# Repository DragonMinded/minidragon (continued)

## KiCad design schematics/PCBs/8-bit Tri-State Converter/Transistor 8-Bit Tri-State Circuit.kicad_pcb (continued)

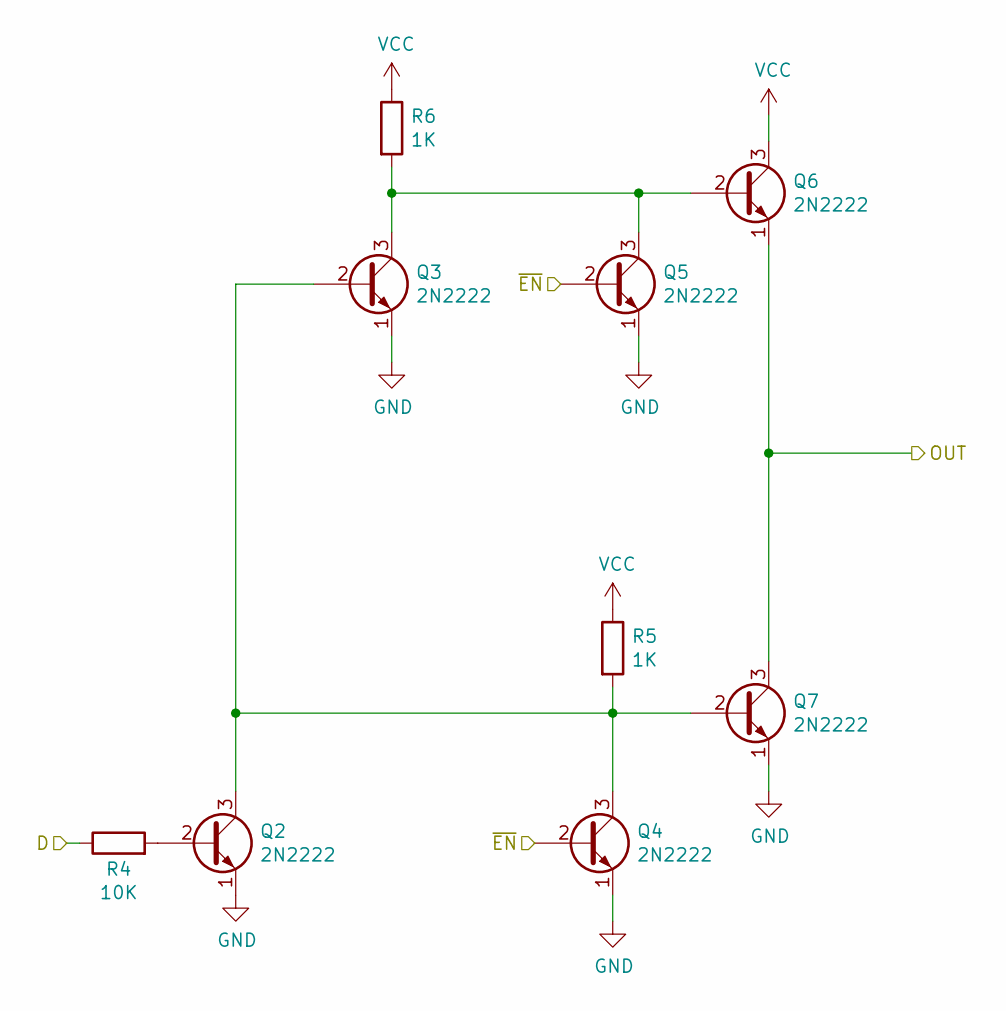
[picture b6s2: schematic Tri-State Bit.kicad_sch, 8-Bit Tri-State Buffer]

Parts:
Q2, Q3, Q4, Q5, Q6, Q7: 2N2222; TO-92_Inline
R4: 10K; R_Axial_DIN0309_L9.0mm_D3.2mm_P12.70mm_Horizontal
R5, R6: 1K; R_Axial_DIN0309_L9.0mm_D3.2mm_P12.70mm_Horizontal

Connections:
D0: R4.1; also elsewhere on the board
GND: Q2.1 (E), Q3.1 (E), Q4.1 (E), Q5.1 (E), Q7.1 (E); also elsewhere on the board
unnamed: Q2.2 (B), R4.2
unnamed: Q2.3 (C), Q3.2 (B), Q4.3 (C), Q7.2 (B), R5.2
unnamed: Q3.3 (C), Q5.3 (C), Q6.2 (B), R6.2
Q0: Q6.1 (E), Q7.3 (C); also elsewhere on the board
VCC: Q6.3 (C), R5.1, R6.1; also elsewhere on the board
~EN_BUF: Q4.2 (B), Q5.2 (B); also elsewhere on the board

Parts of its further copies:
Q8, Q9, Q10, Q11, Q12, Q13, Q14, Q15, Q16, Q17, Q18, Q19, Q20, Q21, Q22, Q23, Q24, Q25, Q26, Q27, Q28, Q29, Q30, Q31, Q32, Q33, Q34, Q35, Q36, Q37, Q38, Q39, Q40, Q41, Q42, Q43, Q44, Q45, Q46, Q47, Q48, Q49: 2N2222; TO-92_Inline
R7, R10, R13, R16, R19, R22, R25: 10K; R_Axial_DIN0309_L9.0mm_D3.2mm_P12.70mm_Horizontal
R8, R9, R11, R12, R14, R15, R17, R18, R20, R21, R23, R24, R26, R27: 1K; R_Axial_DIN0309_L9.0mm_D3.2mm_P12.70mm_Horizontal

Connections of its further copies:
D1: R7.1; also elsewhere on the board
D2: R10.1; also elsewhere on the board
D3: R13.1; also elsewhere on the board
D4: R16.1; also elsewhere on the board
D5: R19.1; also elsewhere on the board
D6: R22.1; also elsewhere on the board
D7: R25.1; also elsewhere on the board
GND: Q8.1 (E), Q9.1 (E), Q10.1 (E), Q11.1 (E), Q13.1 (E), Q14.1 (E), Q15.1 (E), Q16.1 (E), Q17.1 (E), Q19.1 (E), Q20.1 (E), Q21.1 (E), Q22.1 (E), Q23.1 (E), Q25.1 (E), Q26.1 (E), Q27.1 (E), Q28.1 (E), Q29.1 (E), Q31.1 (E), Q32.1 (E), Q33.1 (E), Q34.1 (E), Q35.1 (E), Q37.1 (E), Q38.1 (E), Q39.1 (E), Q40.1 (E), Q41.1 (E), Q43.1 (E), Q44.1 (E), Q45.1 (E), Q46.1 (E), Q47.1 (E), Q49.1 (E); also elsewhere on the board
unnamed: Q8.2 (B), R7.2
unnamed: Q8.3 (C), Q9.2 (B), Q10.3 (C), Q13.2 (B), R8.2
unnamed: Q9.3 (C), Q11.3 (C), Q12.2 (B), R9.2
unnamed: Q14.2 (B), R10.2
unnamed: Q14.3 (C), Q15.2 (B), Q16.3 (C), Q19.2 (B), R11.2
unnamed: Q15.3 (C), Q17.3 (C), Q18.2 (B), R12.2
unnamed: Q20.2 (B), R13.2
unnamed: Q20.3 (C), Q21.2 (B), Q22.3 (C), Q25.2 (B), R14.2
unnamed: Q21.3 (C), Q23.3 (C), Q24.2 (B), R15.2
unnamed: Q26.2 (B), R16.2
unnamed: Q26.3 (C), Q27.2 (B), Q28.3 (C), Q31.2 (B), R17.2
unnamed: Q27.3 (C), Q29.3 (C), Q30.2 (B), R18.2
unnamed: Q32.2 (B), R19.2
unnamed: Q32.3 (C), Q33.2 (B), Q34.3 (C), Q37.2 (B), R20.2
unnamed: Q33.3 (C), Q35.3 (C), Q36.2 (B), R21.2
unnamed: Q38.2 (B), R22.2
unnamed: Q38.3 (C), Q39.2 (B), Q40.3 (C), Q43.2 (B), R23.2
unnamed: Q39.3 (C), Q41.3 (C), Q42.2 (B), R24.2
unnamed: Q44.2 (B), R25.2
unnamed: Q44.3 (C), Q45.2 (B), Q46.3 (C), Q49.2 (B), R26.2
unnamed: Q45.3 (C), Q47.3 (C), Q48.2 (B), R27.2
Q1: Q12.1 (E), Q13.3 (C); also elsewhere on the board
Q2: Q18.1 (E), Q19.3 (C); also elsewhere on the board
Q3: Q24.1 (E), Q25.3 (C); also elsewhere on the board
Q4: Q30.1 (E), Q31.3 (C); also elsewhere on the board
Q5: Q36.1 (E), Q37.3 (C); also elsewhere on the board
Q6: Q42.1 (E), Q43.3 (C); also elsewhere on the board
Q7: Q48.1 (E), Q49.3 (C); also elsewhere on the board
VCC: Q12.3 (C), Q18.3 (C), Q24.3 (C), Q30.3 (C), Q36.3 (C), Q42.3 (C), Q48.3 (C), R8.1, R9.1, R11.1, R12.1, R14.1, R15.1, R17.1, R18.1, R20.1, R21.1, R23.1, R24.1, R26.1, R27.1; also elsewhere on the board
~EN_BUF: Q10.2 (B), Q11.2 (B), Q16.2 (B), Q17.2 (B), Q22.2 (B), Q23.2 (B), Q28.2 (B), Q29.2 (B), Q34.2 (B), Q35.2 (B), Q40.2 (B), Q41.2 (B), Q46.2 (B), Q47.2 (B); also elsewhere on the board

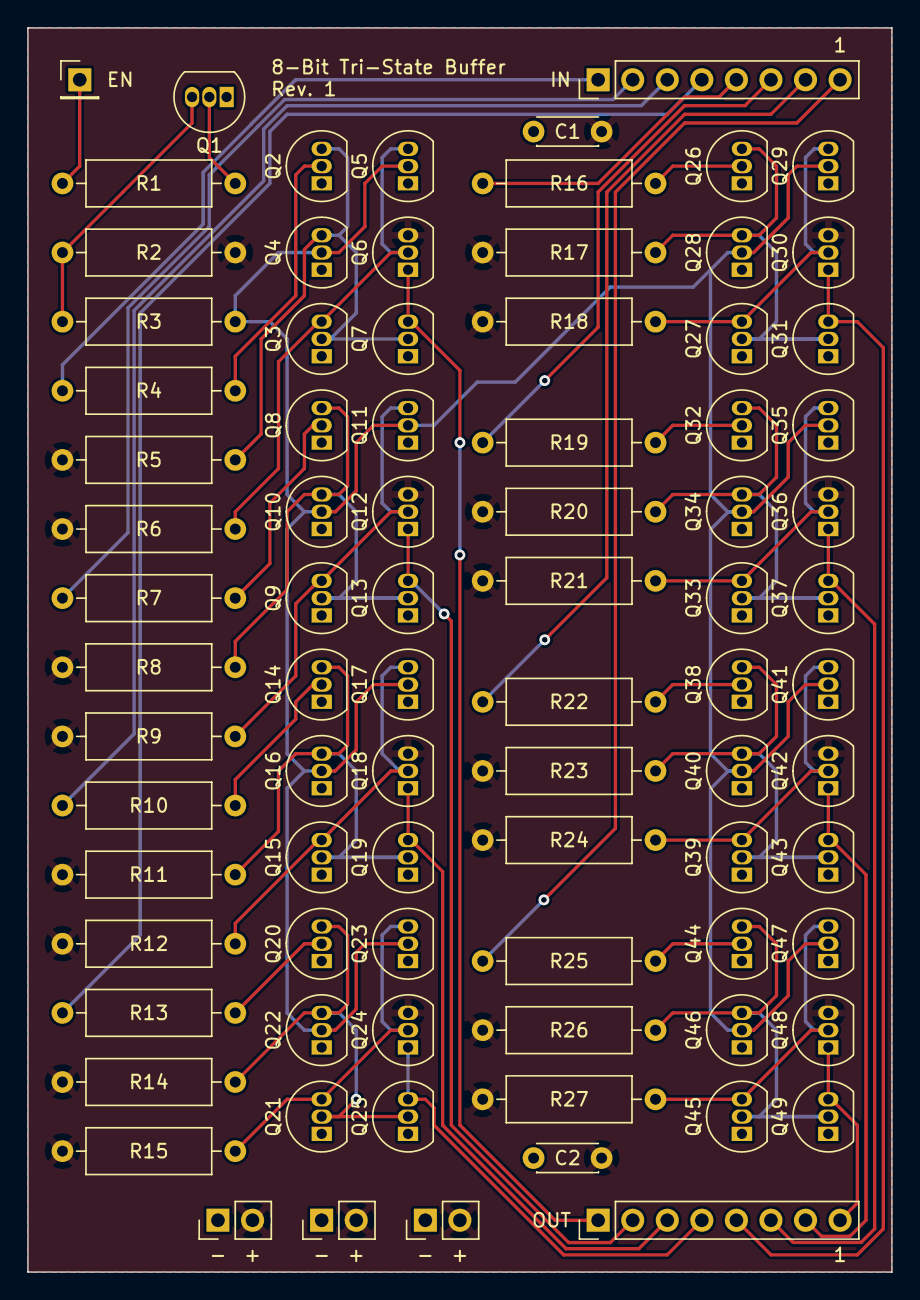
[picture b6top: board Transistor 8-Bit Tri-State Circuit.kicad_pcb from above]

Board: 2 copper layers, 63.5 x 91.4 mm, 84 parts (0 on the bottom side), 46 nets.

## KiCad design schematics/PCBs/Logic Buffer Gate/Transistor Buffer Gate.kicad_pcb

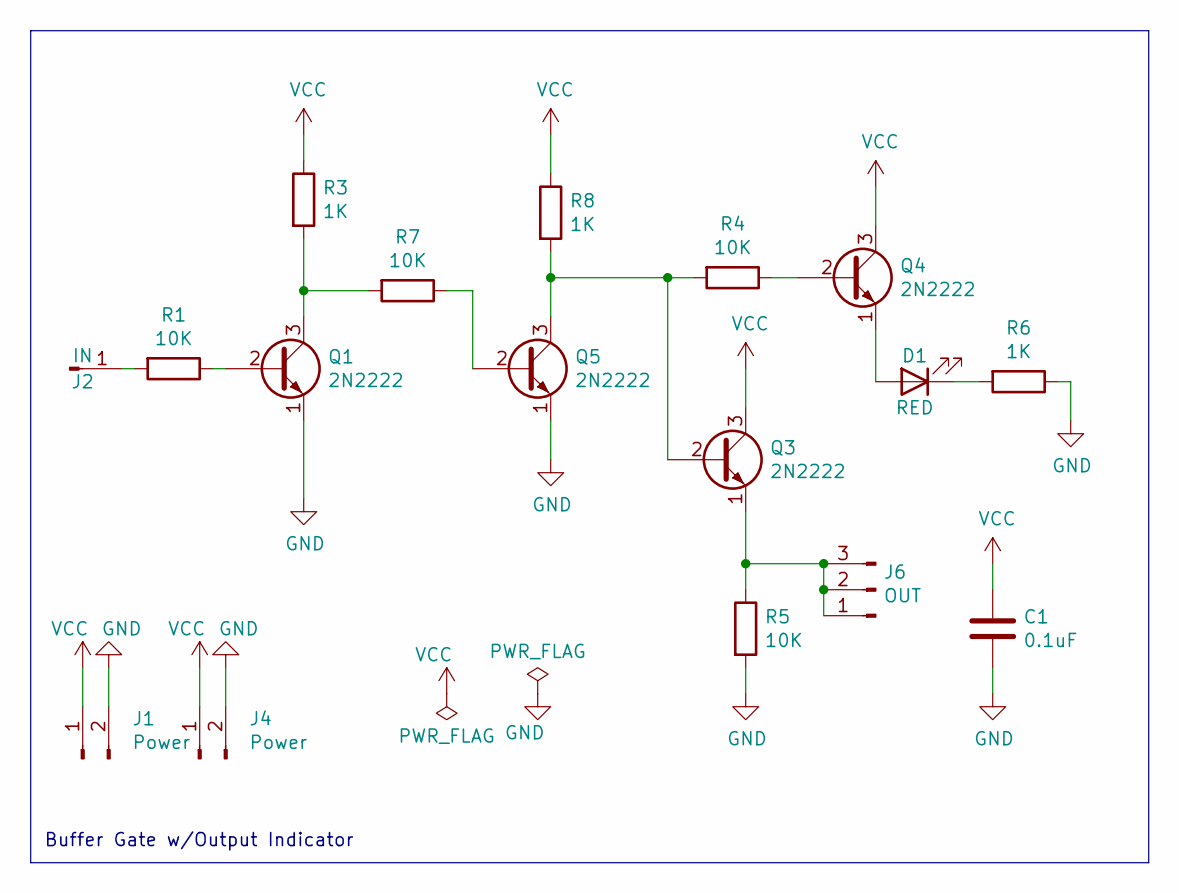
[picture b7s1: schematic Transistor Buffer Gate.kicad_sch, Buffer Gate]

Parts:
C1: 0.1uF; C_Disc_D4.3mm_W1.9mm_P5.00mm
D1: RED; LED_D5.0mm
J1, J4: Power; PinHeader_1x02_P2.54mm_Vertical
J2: IN; PinHeader_1x01_P2.54mm_Vertical
J6: OUT; PinHeader_1x03_P2.54mm_Vertical
Q1, Q3, Q4, Q5: 2N2222; TO-92_Inline
R1, R4, R5, R7: 10K; R_Axial_DIN0309_L9.0mm_D3.2mm_P12.70mm_Horizontal
R3, R6, R8: 1K; R_Axial_DIN0309_L9.0mm_D3.2mm_P12.70mm_Horizontal

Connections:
GND: C1.2, J1.2, J4.2, Q1.1 (E), Q5.1 (E), R5.2, R6.1
unnamed: D1.2 (A), Q4.1 (E)
unnamed: D1.1 (K), R6.2
unnamed: J2.1, R1.2
unnamed: J6.1, J6.2, J6.3, Q3.1 (E), R5.1
unnamed: Q1.2 (B), R1.1
unnamed: Q1.3 (C), R3.2, R7.2
unnamed: Q3.2 (B), Q5.3 (C), R4.2, R8.2
unnamed: Q4.2 (B), R4.1
unnamed: Q5.2 (B), R7.1
VCC: C1.1, J1.1, J4.1, Q3.3 (C), Q4.3 (C), R3.1, R8.1

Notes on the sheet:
Buffer Gate w/Output Indicator

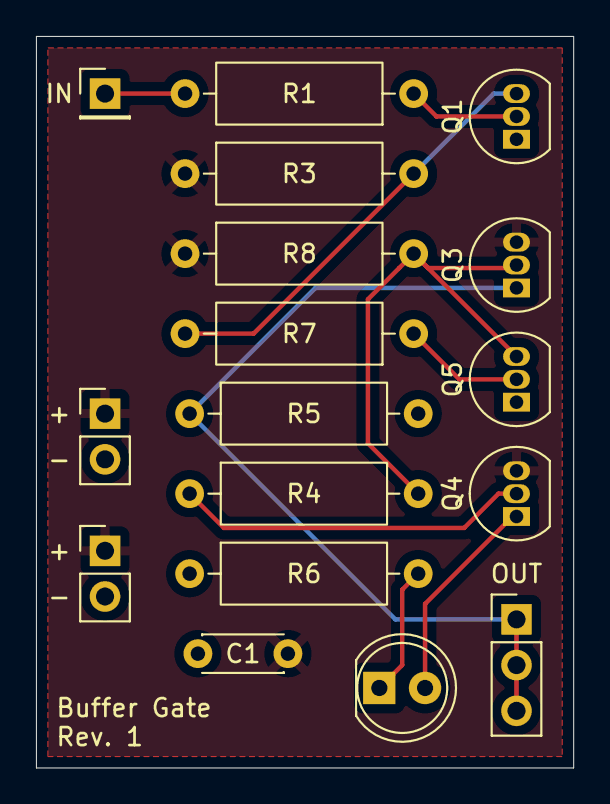
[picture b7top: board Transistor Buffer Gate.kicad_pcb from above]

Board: 2 copper layers, 29.8 x 40.6 mm, 17 parts (0 on the bottom side), 11 nets.

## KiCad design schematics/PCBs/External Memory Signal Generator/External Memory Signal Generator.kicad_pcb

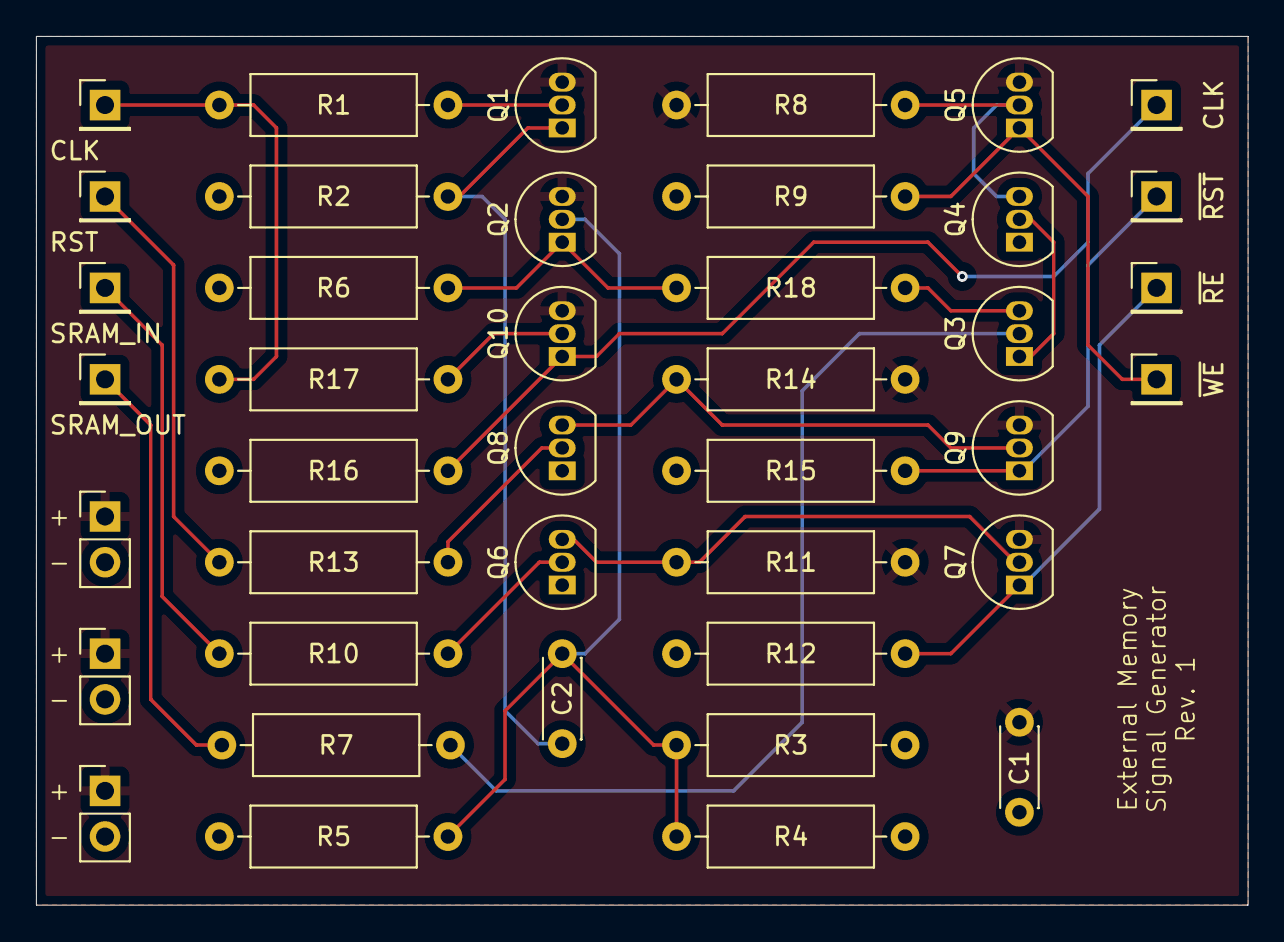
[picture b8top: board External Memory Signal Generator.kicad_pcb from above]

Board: 2 copper layers, 67.3 x 48.3 mm, 41 parts (0 on the bottom side), 23 nets.

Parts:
C1, C2: 0.1uF; C_Disc_D4.3mm_W1.9mm_P5.00mm
J1, J11: CLK; PinHeader_1x01_P2.54mm_Vertical
J2: RST; PinHeader_1x01_P2.54mm_Vertical
J3: SRAM_IN; PinHeader_1x01_P2.54mm_Vertical
J4: SRAM_OUT; PinHeader_1x01_P2.54mm_Vertical
J5: ~{WE}; PinHeader_1x01_P2.54mm_Vertical
J6, J7, J8: Power; PinHeader_1x02_P2.54mm_Vertical
J9: ~{RE}; PinHeader_1x01_P2.54mm_Vertical
J10: ~{RST}; PinHeader_1x01_P2.54mm_Vertical
Q1, Q2, Q3, Q4, Q5, Q6, Q7, Q8, Q9, Q10: 2N2222; TO-92_Inline
R1, R6, R8, R11, R14, R17: 1K; R_Axial_DIN0309_L9.0mm_D3.2mm_P12.70mm_Horizontal
R2, R3, R4, R5, R9, R12, R15, R16, R18: 100; R_Axial_DIN0309_L9.0mm_D3.2mm_P12.70mm_Horizontal
R7, R10, R13: 10K; R_Axial_DIN0309_L9.0mm_D3.2mm_P12.70mm_Horizontal

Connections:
/CLK: J1.1, R1.2, R17.2
/CLOCK: J11.1, Q10.1 (E), R16.1
/RST: J2.1, R13.2
/SRAM_IN: J3.1, R10.2
/SRAM_OUT: J4.1, R7.2
/~RESET: J10.1, Q9.1 (E), R15.1
/~RE: J9.1, Q7.1 (E), R12.1
/~WE: J5.1, Q5.1 (E), R9.1
GND: C1.1, J6.2, J7.2, J8.2, Q4.1 (E), Q6.1 (E), Q8.1 (E), R2.2, R3.2, R4.2, R5.2, R6.2, R9.2, R12.2, R15.2, R16.2
unnamed: Q1.2 (B), R1.1
unnamed: C2.1, Q1.1 (E), R2.1
unnamed: C2.2, Q2.2 (B), R3.1, R4.1, R5.1
unnamed: Q2.1 (E), R6.1, R18.1
unnamed: Q3.2 (B), R7.1
unnamed: Q3.3 (C), R18.2
unnamed: Q3.1 (E), Q4.2 (B)
unnamed: Q4.3 (C), Q5.2 (B), R8.2
unnamed: Q6.2 (B), R10.1
unnamed: Q6.3 (C), Q7.2 (B), R11.2
unnamed: Q8.2 (B), R13.1
unnamed: Q8.3 (C), Q9.2 (B), R14.2
unnamed: Q10.2 (B), R17.1
VCC: C1.2, J6.1, J7.1, J8.1, Q1.3 (C), Q2.3 (C), Q5.3 (C), Q7.3 (C), Q9.3 (C), Q10.3 (C), R8.1, R11.1, R14.1

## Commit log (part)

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2025-05-25 Refactor binary operations out to their own function.
2025-05-25 Implement 8/16/32 bit multiplication expressions, add support for signed/unsigned tracking.
2025-05-26 Handle local constants a bit more intelligently.
2025-05-26 Implement unsigned integer division expression evaluation.
2025-05-26 Skip on signed integer division until such time as I actually need it.
2025-05-26 Implement modulo support.
2025-05-27 Better comments for negation within expressions.
2025-05-28 Update global variables and local constants to keep types around.
2025-05-28 Support assigning function returns to different variable sizes.
2025-05-28 Implement simple is check comparisons, switch back from "boolean" to "bool".
2025-05-29 Implement boolean not expressions.
2025-05-29 Move to only ever inserting extras with environment variables.
2025-05-30 Slight optimization for return value handling.
2025-05-30 Implement same-size equality and inequality expressions.
2025-05-31 Fix TODO that is incorrect after I implemented not awhile back.
2025-06-02 Add bit shifting operations to TODO list.
2025-06-05 Initial implementation of global variables, with tests for reading.
2025-06-06 Support calling void functions without assigning a return value.
2025-06-07 Add another test case that I just thought about.
2025-06-07 Add another wishlist item.
2025-06-07 Local variable initialization tracking with compiler error for use before init.
2025-06-07 Initial implmementation of while loops. Still missing else flow.
2025-06-08 Implement for x in range() style for statements. No else clause support yet.
2025-06-09 Begin work on strings, starting with string pointer lookup and ability to define global constant and non-constant strings.
2025-06-10 Implement local and global string assignment, including local storage space for functions to store non-const strings.
2025-06-15 Implement len() for string length calculations.
2025-06-15 Implement string concatenation using the + operator.
2025-06-15 Implement indexing into a string by integer to get a character.
2025-06-15 Mark down a new TODO which could lead to some optimizations.
2025-06-16 Add ability for CPU core to track and print changed fields.
2025-06-17 Implement character and string comparisons.
2025-06-18 Implement character updating for strings, fix global statement not propagating to indented bodies.
2025-06-19 Implement unsigned variants of itoa for upcoming str() handling.
2025-06-19 Implement simple f-string support (no conversion spec, no format spec).
2025-06-20 Implement shift helper functions in the math stdlib.
2025-06-22 Update documentation with discussion on finalized memory map.
2025-06-24 Implement peek() with support for all implemented types.
2025-06-24 Switch to different unrolled memcpy variant to save a few cycles here and there.
2025-06-28 Explicitly rename stdlib functions with no suffix to "8" suffix.
2025-07-11 Implement bool() builtin.
2025-07-11 Implement boolean coercing for ternary expressions.
2025-08-21 Implement ord() built-in function.
2025-08-22 Add tests and handling to ensure non-const string references to int get advanced.
2025-08-22 Implement signed versions of stdlib min/max variants.
2025-08-22 Update TODO.
2025-08-24 Remove old buildrom script, replace with an actual makefile and beginning of a bootrom directory.
2025-08-25 Empty string initialization is much faster now.
2025-08-27 Redundant store/load removal optimization, coupled with redundant stack move operation optimization.
2025-08-27 Implement if/while/for statement boolean check optimization.
2025-08-27 Update TODOs.
2025-09-28 Update microcode generator and relevant constants for upcoming inverting control signals distributor.
2025-09-28 Update layout to indicate MCODE_RST is no longer a negative signal, remove NOT gate handling it.
2025-10-14 Support docstrings in python compiled code.
2025-10-14 Start on serial driver code for bootROM.
2025-10-14 Improve listing comments by removing duplicates.
2025-10-14 Fix stdin emulated serial buffering until return character sent.
2025-10-15 Fix for escape sequences in non-const literals not getting evaluated correctly.
2025-10-15 Update to bootROM to allow prompting for input and reading from serial.
2025-10-15 Fix invalid string length for constants, fix error not generated in some specific edge cases for non-constant string returns.
2025-10-15 Remove compiler bug workaround from bootROM.
2025-10-15 Another optimization opportunity for boolean evaluation.
2025-10-15 Take advantage of default argument values to make the serial library better.
2025-10-16 Use kwargs and default args to do something slightly more interesting in bootROM.
2025-10-16 Prefix local storage labels so they do not appear in the bootROM symbol table.
2025-10-19 Put in (currently unneeded) Rx/Tx impossible condition logs.
2025-10-19 Translate 0x7F to 0x08 when emulating terminal with modern linux.
2025-10-19 Fix NEG/INV constant folding optimization which I noticed was broken.
2025-10-20 Add a test for complex string expressions, fix a few spots in the compiler not allowing it to work.
2025-10-20 Implement same-variable truncation optimization.
2025-10-20 More correct line sanitization in compiler optimizer.
2025-10-20 Move to a helper function for moving pos along in optimizer.
2025-10-20 Make all optimization code lookup functions aware of comments by offsetting by logical code lines.
2025-10-21 Fix emulated VT-100 with linux terminal behaving wrong with escape sequence receipt.
2025-10-21 Implement flow control in MiniDragon serial library.
2025-10-21 Implement subscript optimization when variable is local.
2025-10-21 Fix receive timing in serial emulated version to match observed VT-102 behavior.
2025-10-21 Optimize escape code read/clear code to keep up with real VT-102 hardware when simulating actual MiniDragon speeds.
2025-10-21 Auto-coerce non-bools in and/or boolean expressions.
2025-10-21 Receive buffer should not be longer than maximum allowed string.
2025-10-28 Implement temporary string reuse between expressions to save space in RAM.
2025-10-29 Update documentation, add eratta section.
2025-10-29 Refactor make file and lib/bootrom organization a bit to make it easier to have multiple top-level targets.
2025-10-29 Fix terminal needing reset after exiting cleanly if emulating a VT-100.
2025-10-31 Fix potential compiler assertion error by categorizing a few missed stores.
2025-10-31 Fix memory safety of optimized string truncation.
2025-11-01 Apply boolean optimization in more cases.
2025-11-01 Fix inability to extern a function, unclear how tests verifying this didn't catch the problem.
2025-11-01 Fix tests after void type fixup.
2025-11-05 Bump emulator clock speed to match new clock circuit IRL.
2025-11-06 Update completion based on some physical board progress.
2025-11-06 Move sanitize into assembler, use it where we want sanitized lines.
2025-11-06 Add fixed point library, currently only containing strtofixed and fixedtostr.
2025-11-06 Some slight fast-path stuff for fixed width, get rid of precision argument for strtofixed.
2025-11-07 Use fixed() intrinsic in fixed test ROM.
2025-11-08 Fixed conversion routines are now correct over a much wider range of numbers.
2025-11-09 Fix function returning string not strcpying to destinations that aren't const.
2025-11-09 Use newly-minted string iterators for fixed width library.
2025-11-11 Add another TODO.
2025-11-13 Implement cast() support for going between uint16 and str, mostly for peek/poke use.
2025-11-13 Ensure function returns with a string don't do an unnecessary strcpy.
2025-11-14 Check in initial langauge specification.
2025-11-14 Fix some formatting.
2025-11-15 Add concept of library directories to compiler, move fixed and serial code to lib/
2025-11-15 Attempt another method at indenting paragraphs.
2025-11-15 Waffle on location of fixed conversion library.
2025-11-15 Additional string clarification.
2025-11-16 Fix cast() not correctly taking address of local string variables, fix tests broken by previous commit.
2025-11-16 - Move example bootrom to roms directory - Move bootrom makefile to its source directory - Introduce a set of path variables to makefile to make it easier to configure - Configure makefile to run fro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
    Now one can simply copy the example bootrom folder to write ones own rom
2025-11-16 - remove stupid mistake
2025-11-16 Move executables into entrypoints, make top level executables into simple shell scripts instead of require running with python.
2025-11-16 Ignore setuptools egg info file when installing.
2025-11-16 Allow for more returns that don't need to specify a string length.
2025-11-16 Surround compiler functions in a class so we stop mutating the global state when compiling.
2025-11-16 Bump revision.
2025-11-17 Make use of sys module in boot ROM for displaying system version.
2025-11-17 Remove debugging I left in on accident.
2025-11-18 Swap parameters to enum from set of booleans to easier catch commenting misuse.
2025-11-22 Add examples of function calls in MiniPy language specification.
2025-11-22 Document global support.
2025-11-23 Fix bug in serial_send which would attempt to clear echoed characters even when echoing was disabled.
2025-11-23 Try out horizontal rules for separating sections.
2025-11-23 Additional separation for other sections.
2025-11-24 Implement trivial dead code optimization in a spot that doesn't matter.
2025-11-25 Fix string operations where the variable is on the RHS not in the leftmost position.
2025-11-25 Fix type narrowing in signed types with if expressions.
2025-11-26 Fix inability to specify high addresses in assembler and simulator.
2025-11-26 Add a skeleton cartridge directory which works with an installed version of this repo, update boot ROM to list out and launch cartridges.
2025-11-26 Fix formatting for cartridge README.
2025-11-26 Bump revision to keep released boot ROM for cartridges in line with fixes to stdlib.
2025-11-27 Add a debug register to the CCR space for helping profile algorithms.
2025-11-27 Fix validation suite to match expectations of RAM locations.
2025-12-02 Allow raw strings, support bytestrings.
2025-12-03 Slight speedup on serial_send by using string iterator.
2025-12-16 Add a couple of new useful bits to the compiler ecosystem.
    Add a generator program for converting binary data to global const assembly that can be compiled into a program.
    Update to allow for extern constants, so externs can point at code instead of data safely.
2026-01-16 Add symbols for new boards to be used with layout diagram.
2026-01-16 Bugfix crossed connections on layout main data bus.
2026-01-19 Add .ptr directive to point at another label in .S files.
2026-01-21 Add a couple more upcoming boards so I can use them in planning diagrams.
2026-02-16 Update README with progress that has been made.
2026-03-14 Update with new Shift symbol, diagram the rest of the ALU and more instruction decoder boards.
2026-06-25 Documentation updates
    Update README with newly discovered eratta.
    Update PCBs directory to include 3 newer PCBs that were missing.
    Update layout to reflect SHL/SHR stability fixes.
2026-06-27 Update compiler to properly support full byte length strings.
2026-06-28 Implement wstrlen stdlib function.
2026-06-28 Add wide string variants to compiler intrinsics after testing with a local test program.
2026-06-30 Update language specification to reflect that strings can be much longer now.
2026-06-30 Fix typo in language specification.
2026-06-30 Implement 16-bit string indexes for character lookup.
2026-06-30 Update language specification stdlib docs.
2026-06-30 Fix inability to call peek with second parameter that's also an intrinsic like len.
2026-06-30 Update peek to be 16-bit string aware.
2026-06-30 Implement 16-bit len() support, for when the destination is a (u)int16 or (u)int32.
2026-06-30 Speed up entering keys and backspacing on input prompt.
2026-06-30 Fix string mutate assignment codegen wrong for expressions that clobber SPC, add support for 16-bit string offsets for mutate assignment.
